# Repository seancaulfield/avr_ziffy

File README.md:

avr_ziffy
=========

Arduino shield with a plethora of ZIF sockets to allow programming of all the
various Atmel AVR chips.

The hardware directory should contain the Eagle CAD project files needed to
build the board. Since they're Not Exactly Code but still open hardware, I'm
licensing them under Creative Commons Attribution Share Alike license.

I've modified the sample code provided with the Arduino distribution for the
firmware files, both because I needed to ensure all the pins would line up and
also do fix a few problems/lack of clarity in the source code Sicne this was
originally under a 2-clause BSD license, I will stick to that for my fork of
the code.

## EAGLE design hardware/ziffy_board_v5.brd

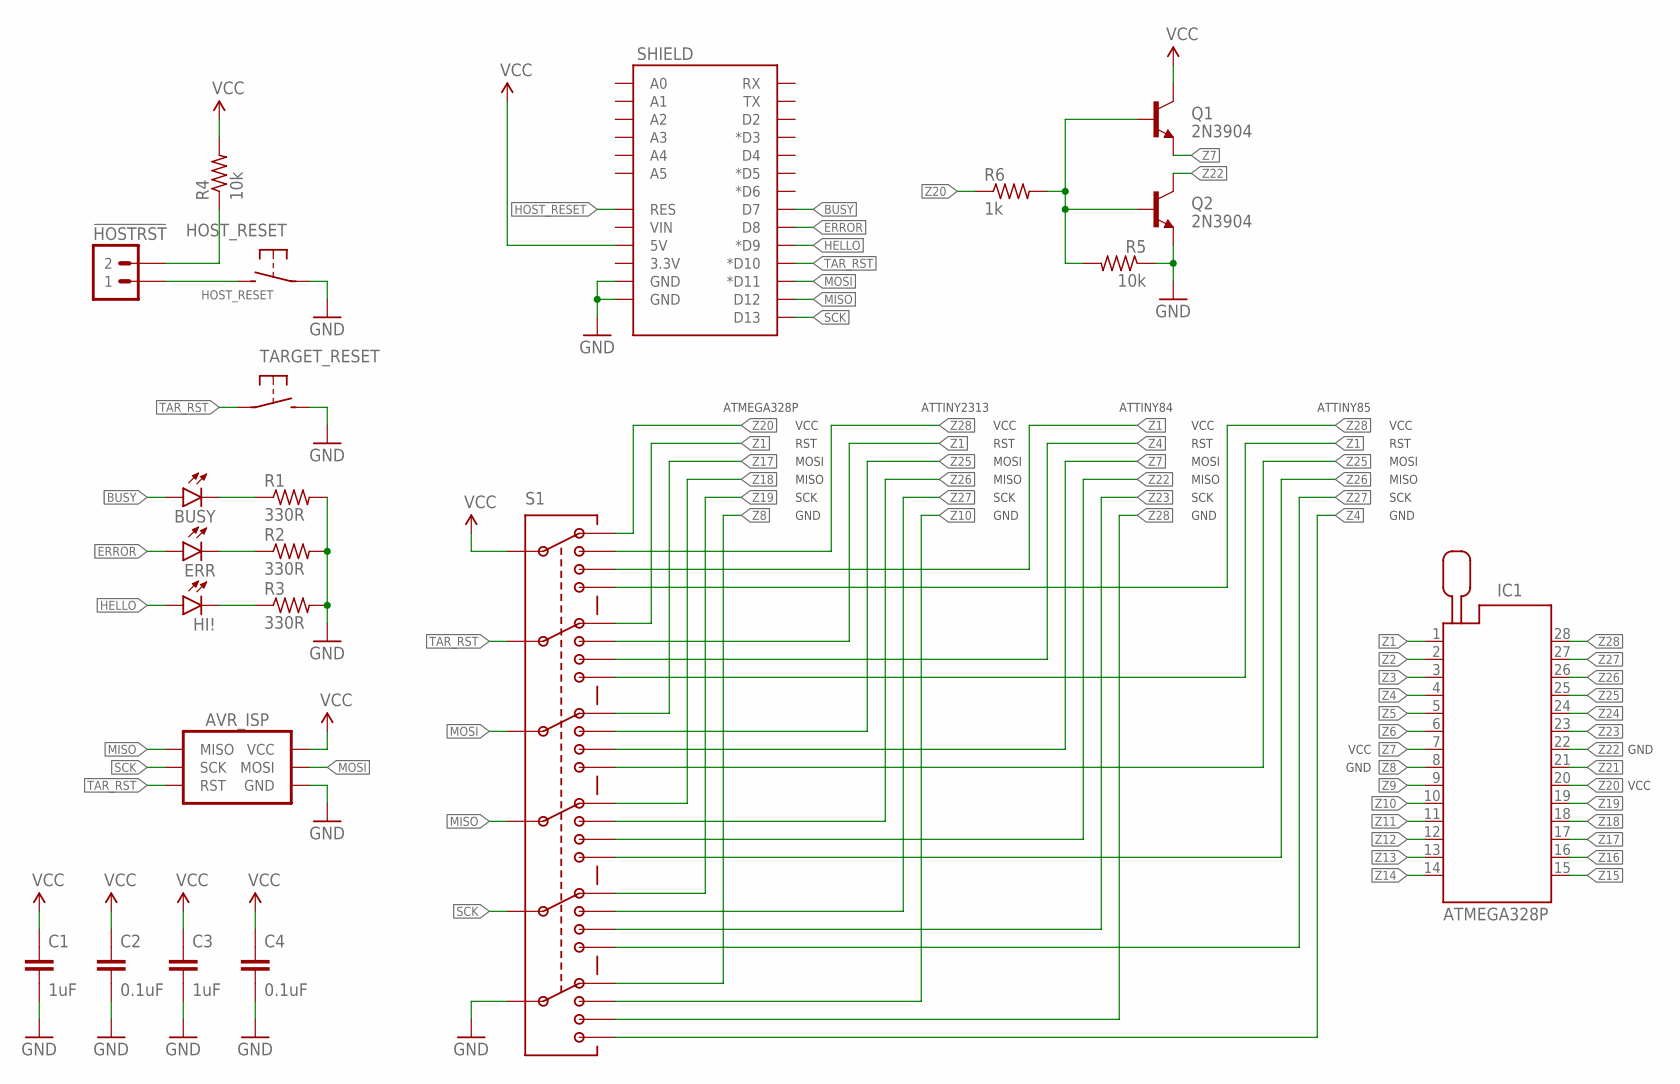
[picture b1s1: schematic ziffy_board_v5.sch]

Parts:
!HOSTRST: M02PTH; 1X02
AVR_ISP: AVR_SPI_PRG_6PTH-SHROUD; 2X3-SHROUDED
BUSY: YELLOW; LED3MM
C1, C3: 1uF; C025-024X044
C2, C4: 0.1uF; C025-024X044
ERR: RED; LED3MM
HI!: GREEN; LED3MM
HOST_RESET: SPST-NO-TACT6MM-PTH-SMALL-PADS; DTS-6-SMALL-PADS
IC1: ATMEGA328P; ZIF28
Q1, Q2: 2N3904; TO-92-AMMO
R1, R2, R3: 330R; RESISTOR-AXIAL-PTH-6.35MM
R4, R5: 10k; RESISTOR-AXIAL-PTH-6.35MM
R6: 1k; RESISTOR-AXIAL-PTH-6.35MM
S1: SWITCH-6P4TASDFADSFSD; SWITCH-6P4T-2MMPTH
SHIELD: ARDUINO_SHIELD_SMALLER; ARDUINO_SHIELD_NOOUTLINE_INSIDE_SMALLER
TARGET_RESET: SPST-NO-TACT6MM-PTH-SMALL-PADS; DTS-6-SMALL-PADS

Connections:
BUSY: BUSY.A, SHIELD.D7
ERROR: ERR.A, SHIELD.D8
GND: AVR_ISP.6 (GND), C1.2, C2.2, C3.2, C4.2, HOST_RESET.1, HOST_RESET.2 (1), Q2.1 (E), R1.P$2 (2), R2.P$2 (2), R3.P$2 (2), R5.P$1 (1), S1.P28 (28), SHIELD.GND@0 (GND), SHIELD.GND@1 (GND), TARGET_RESET.3 (2), TARGET_RESET.4 (2)
HELLO: HI!.A, SHIELD.D9 (*D9)
HOST_RESET: !HOSTRST.1, HOST_RESET.3 (2), HOST_RESET.4 (2), SHIELD.RES
MISO: AVR_ISP.1 (MISO), S1.P18 (18), SHIELD.D12
MOSI: AVR_ISP.4 (MOSI), S1.P13 (13), SHIELD.D11 (*D11)
unnamed: BUSY.K (C), R1.P$1 (1)
unnamed: ERR.K (C), R2.P$1 (1)
unnamed: HI!.K (C), R3.P$1 (1)
unnamed: !HOSTRST.2, R4.P$1 (1)
unnamed: Q1.2 (B), Q2.2 (B), R5.P$2 (2), R6.P$2 (2)
SCK: AVR_ISP.3 (SCK), S1.P23 (23), SHIELD.D13
TAR_RST: AVR_ISP.5 (RST), S1.P8 (8), SHIELD.D10 (*D10), TARGET_RESET.1, TARGET_RESET.2 (1)
VCC: AVR_ISP.2 (VCC), C1.1, C2.1, C3.1, C4.1, Q1.3 (C), R4.P$2 (2), S1.P3 (3), SHIELD.5V
Z1: IC1.1, S1.P4 (4), S1.P6 (6), S1.P7 (7), S1.P10 (10)
Z2: IC1.2
Z3: IC1.3
Z4: IC1.4, S1.P9 (9), S1.P30 (30)
Z5: IC1.5
Z6: IC1.6
Z7: IC1.7, Q1.1 (E), S1.P14 (14)
Z8: IC1.8, S1.P26 (26)
Z9: IC1.9
Z10: IC1.10, S1.P27 (27)
Z11: IC1.11
Z12: IC1.12
Z13: IC1.13
Z14: IC1.14
Z15: IC1.15
Z16: IC1.16
Z17: IC1.17, S1.P11 (11)
Z18: IC1.18, S1.P16 (16)
Z19: IC1.19, S1.P21 (21)
Z20: IC1.20, R6.P$1 (1), S1.P1 (1)
Z21: IC1.21
Z22: IC1.22, Q2.3 (C), S1.P19 (19)
Z23: IC1.23, S1.P24 (24)
Z24: IC1.24
Z25: IC1.25, S1.P12 (12), S1.P15 (15)
Z26: IC1.26, S1.P17 (17), S1.P20 (20)
Z27: IC1.27, S1.P22 (22), S1.P25 (25)
Z28: IC1.28, S1.P2 (2), S1.P5 (5), S1.P29 (29)

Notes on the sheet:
ATMEGA328P
ATTINY2313
ATTINY84
ATTINY85
VCC
RST
MOSI
MISO
SCK
GND

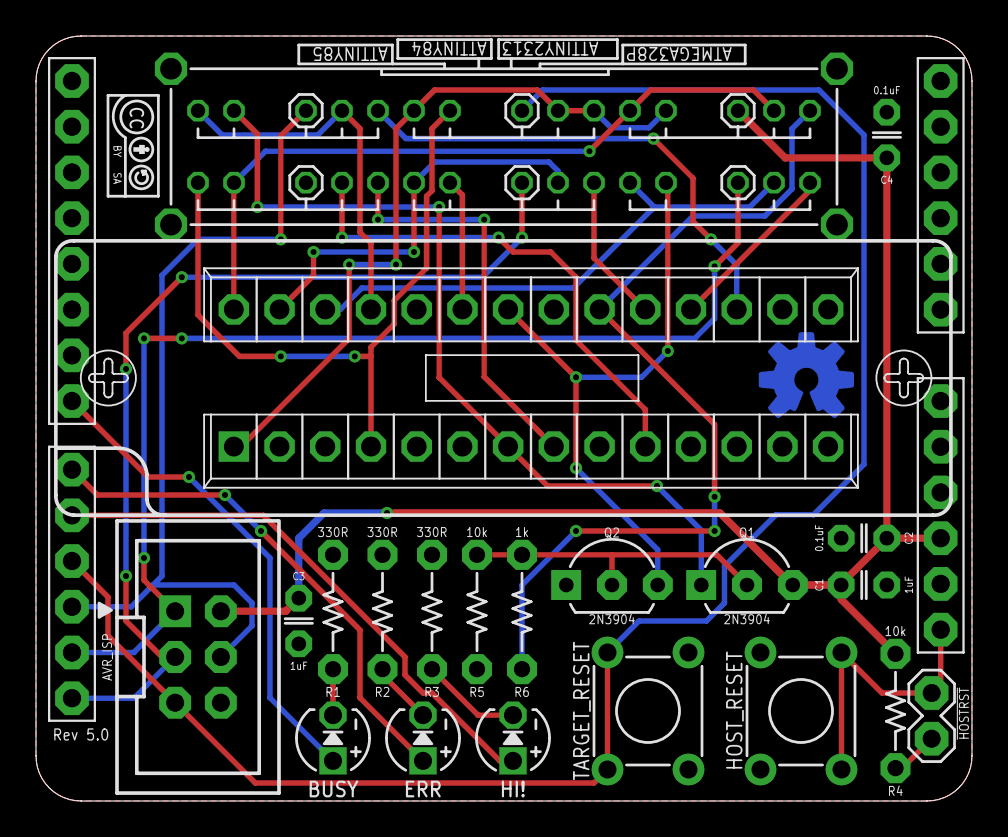
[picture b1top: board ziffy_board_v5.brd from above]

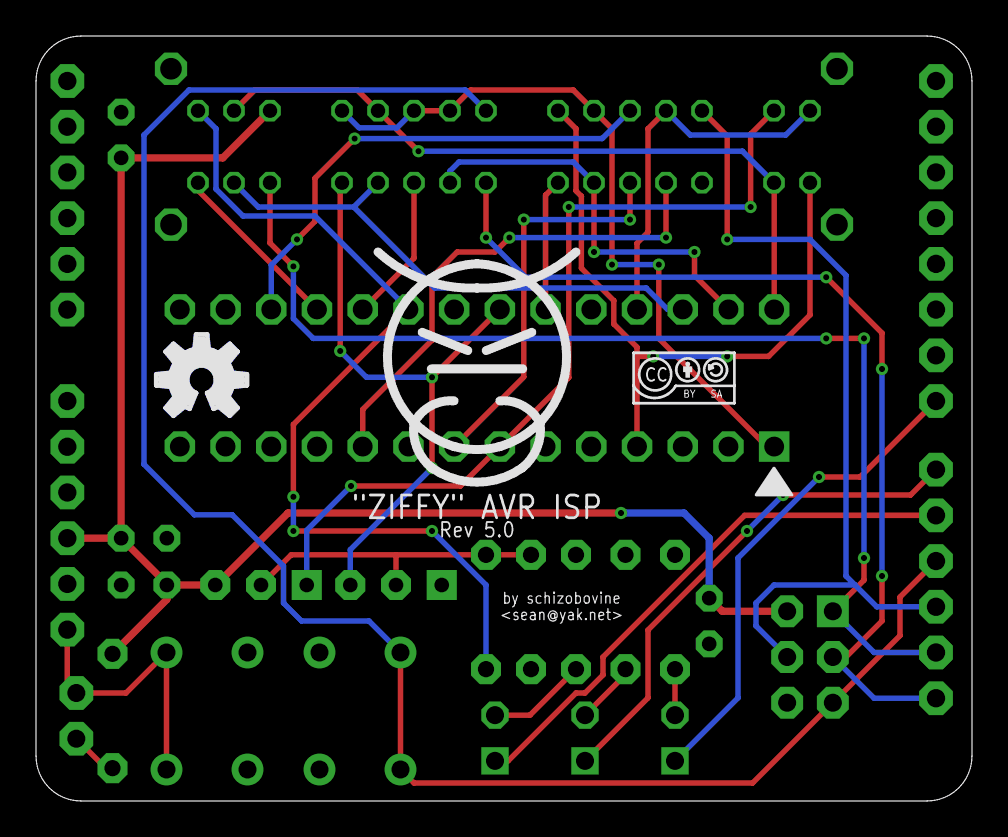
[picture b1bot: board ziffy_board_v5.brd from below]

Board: 2 copper layers, 52.0 x 42.5 mm, 26 parts (2 on the bottom side), 30 nets.

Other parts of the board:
U$1, U$5: CC-BY-SA-4.0-NO-URL
U$2: COW
U$3: OSHWLOGO_BOT_0.2

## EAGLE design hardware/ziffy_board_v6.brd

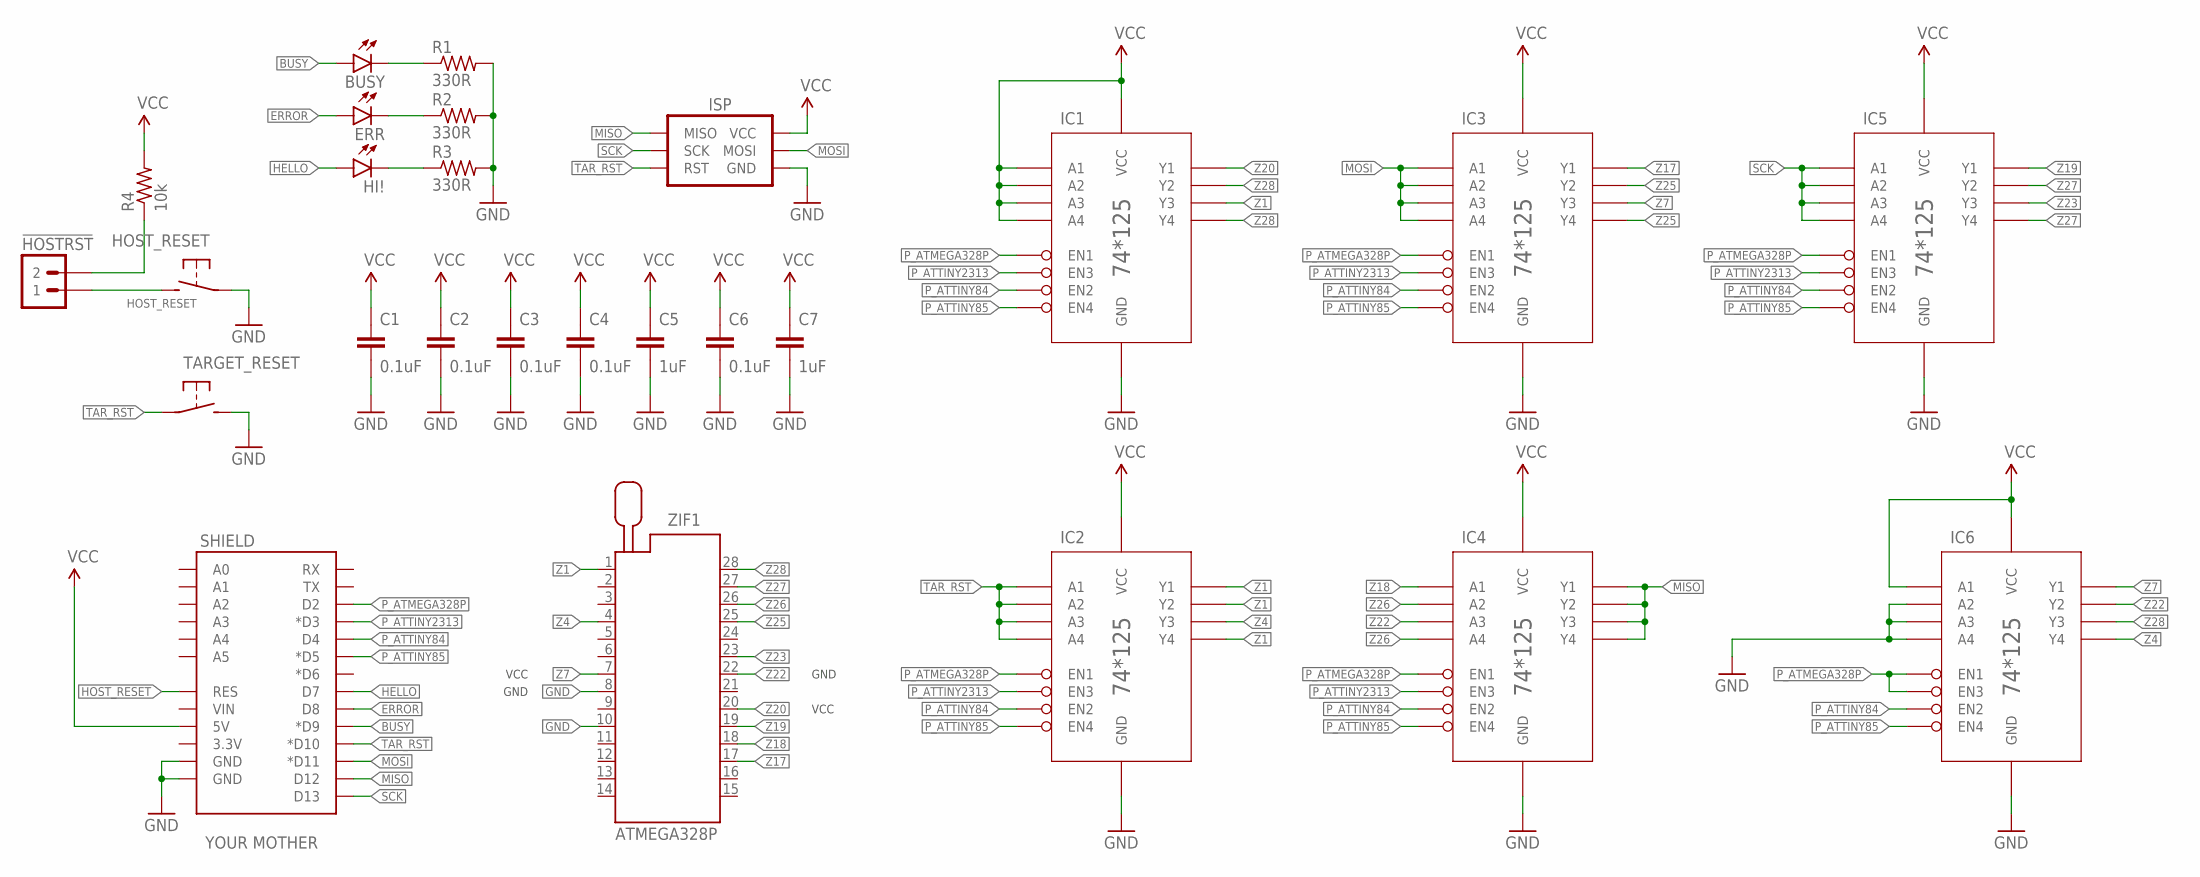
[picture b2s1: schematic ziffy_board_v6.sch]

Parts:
!HOSTRST: M02PTH; 1X02
BUSY: YELLOW; LED3MM
C1, C2, C3, C4, C6: 0.1uF; C025-024X044
C5, C7: 1uF; C025-024X044
ERR: RED; LED3MM
HI!: GREEN; LED3MM
HOST_RESET: SPST-NO-TACT6MM-PTH-SMALL-PADS; DTS-6-SMALL-PADS
IC1, IC2, IC3, IC4, IC5, IC6: 74HC125; SO14
ISP: AVR_SPI_PRG_6PTH-SHROUD; 2X3-SHROUDED
R1, R2, R3: 330R; RESISTOR-AXIAL-PTH-5.08MM
R4: 10k; RESISTOR-AXIAL-PTH-5.08MM
SHIELD: YOUR MOTHER; ARDUINO_SHIELD_NOOUTLINE_INSIDE_SMALLER
TARGET_RESET: SPST-NO-TACT6MM-PTH-SMALL-PADS; DTS-6-SMALL-PADS
ZIF1: ATMEGA328P; ZIF28

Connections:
BUSY: BUSY.A, SHIELD.D9 (*D9)
ERROR: ERR.A, SHIELD.D8
GND: C1.2, C2.2, C3.2, C4.2, C5.2, C6.2, C7.2, HOST_RESET.1, HOST_RESET.2 (1), IC1.7 (GND), IC2.7 (GND), IC3.7 (GND), IC4.7 (GND), IC5.7 (GND), IC6.5 (A2), IC6.7 (GND), IC6.9 (A3), IC6.12 (A4), ISP.6 (GND), R1.P$2 (2), R2.P$2 (2), R3.P$2 (2), SHIELD.GND@0 (GND), SHIELD.GND@1 (GND), TARGET_RESET.3 (2), TARGET_RESET.4 (2), ZIF1.8, ZIF1.10
HELLO: HI!.A, SHIELD.D7
HOST_RESET: !HOSTRST.1, HOST_RESET.3 (2), HOST_RESET.4 (2), SHIELD.RES
MISO: IC4.3 (Y1), IC4.6 (Y2), IC4.8 (Y3), IC4.11 (Y4), ISP.1 (MISO), SHIELD.D12
MOSI: IC3.2 (A1), IC3.5 (A2), IC3.9 (A3), IC3.12 (A4), ISP.4 (MOSI), SHIELD.D11 (*D11)
unnamed: BUSY.K (C), R1.P$1 (1)
unnamed: ERR.K (C), R2.P$1 (1)
unnamed: HI!.K (C), R3.P$1 (1)
unnamed: !HOSTRST.2, R4.P$1 (1)
P_ATMEGA328P: IC1.1 (EN1), IC2.1 (EN1), IC3.1 (EN1), IC4.1 (EN1), IC5.1 (EN1), IC6.1 (EN1), IC6.10 (EN3), SHIELD.D2
P_ATTINY84: IC1.4 (EN2), IC2.4 (EN2), IC3.4 (EN2), IC4.4 (EN2), IC5.4 (EN2), IC6.4 (EN2), SHIELD.D4
P_ATTINY85: IC1.13 (EN4), IC2.13 (EN4), IC3.13 (EN4), IC4.13 (EN4), IC5.13 (EN4), IC6.13 (EN4), SHIELD.D5 (*D5)
P_ATTINY2313: IC1.10 (EN3), IC2.10 (EN3), IC3.10 (EN3), IC4.10 (EN3), IC5.10 (EN3), SHIELD.D3 (*D3)
SCK: IC5.2 (A1), IC5.5 (A2), IC5.9 (A3), IC5.12 (A4), ISP.3 (SCK), SHIELD.D13
TAR_RST: IC2.2 (A1), IC2.5 (A2), IC2.9 (A3), IC2.12 (A4), ISP.5 (RST), SHIELD.D10 (*D10), TARGET_RESET.1, TARGET_RESET.2 (1)
VCC: C1.1, C2.1, C3.1, C4.1, C5.1, C6.1, C7.1, IC1.2 (A1), IC1.5 (A2), IC1.9 (A3), IC1.12 (A4), IC1.14 (VCC), IC2.14 (VCC), IC3.14 (VCC), IC4.14 (VCC), IC5.14 (VCC), IC6.2 (A1), IC6.14 (VCC), ISP.2 (VCC), R4.P$2 (2), SHIELD.5V
Z1: IC1.8 (Y3), IC2.3 (Y1), IC2.6 (Y2), IC2.11 (Y4), ZIF1.1
Z4: IC2.8 (Y3), IC6.11 (Y4), ZIF1.4
Z7: IC3.8 (Y3), IC6.3 (Y1), ZIF1.7
Z17: IC3.3 (Y1), ZIF1.17
Z18: IC4.2 (A1), ZIF1.18
Z19: IC5.3 (Y1), ZIF1.19
Z20: IC1.3 (Y1), ZIF1.20
Z22: IC4.9 (A3), IC6.6 (Y2), ZIF1.22
Z23: IC5.8 (Y3), ZIF1.23
Z25: IC3.6 (Y2), IC3.11 (Y4), ZIF1.25
Z26: IC4.5 (A2), IC4.12 (A4), ZIF1.26
Z27: IC5.6 (Y2), IC5.11 (Y4), ZIF1.27
Z28: IC1.6 (Y2), IC1.11 (Y4), IC6.8 (Y3), ZIF1.28

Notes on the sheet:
VCC
GND

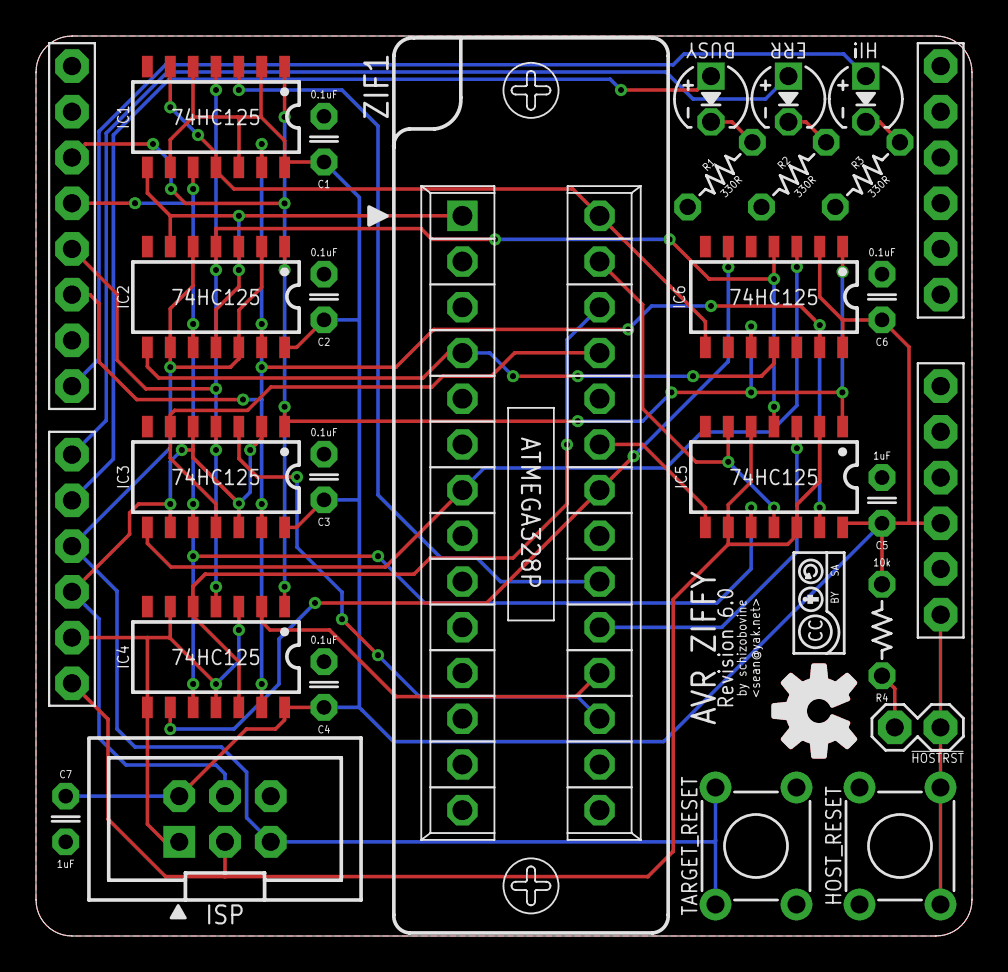
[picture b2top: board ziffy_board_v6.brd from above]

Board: 2 copper layers, 52.0 x 50.0 mm, 28 parts (0 on the bottom side), 31 nets.

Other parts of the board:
U$1: CC-BY-SA-4.0-NO-URL
U$2: OSHWLOGO_TOP_0.2_A

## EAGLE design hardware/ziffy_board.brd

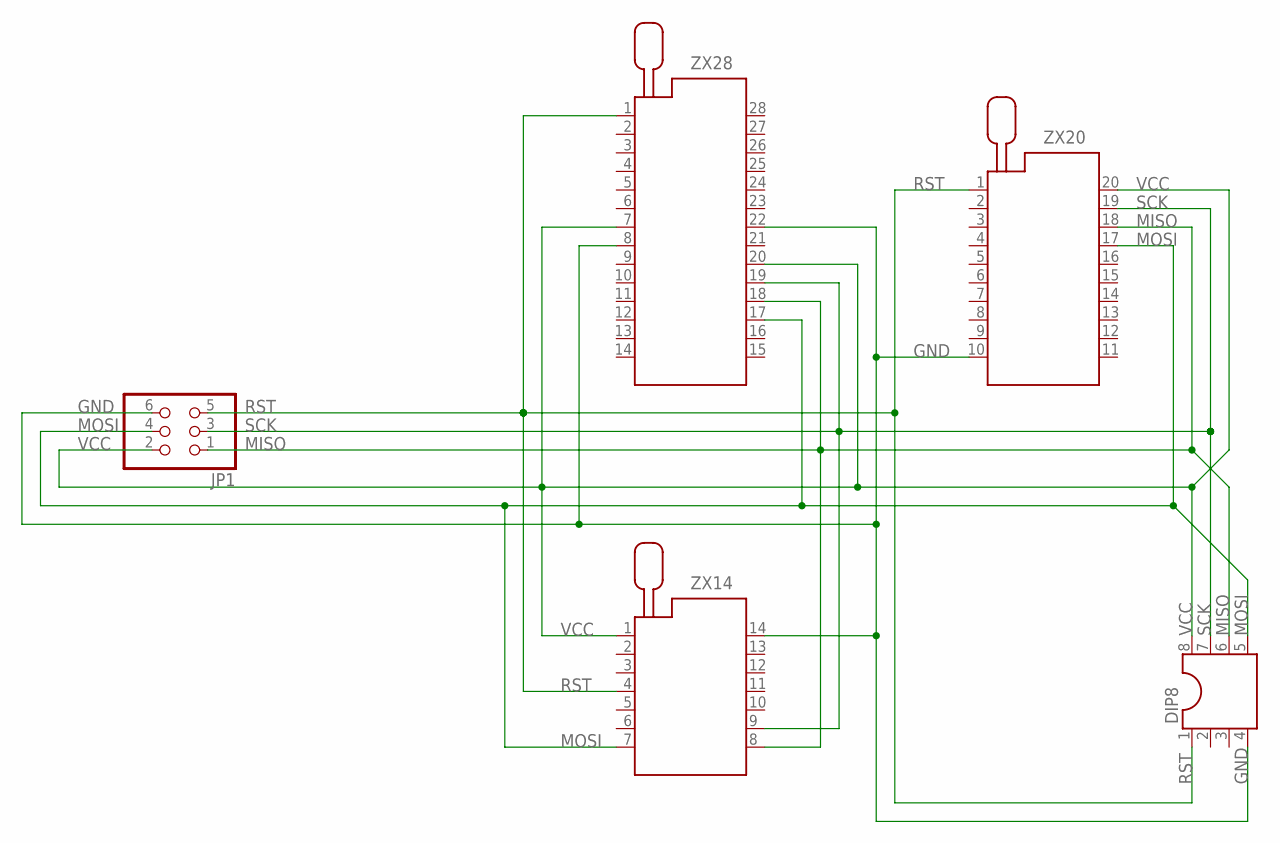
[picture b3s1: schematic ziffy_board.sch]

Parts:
DIP8: DIL8S; SOCKET-08
JP1: PINHD-2X3; 2X03
ZX14: 214-3339-00-0602J
ZX20: 220-3342-00-0602J
ZX28: 228-4817-00-0602J

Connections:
GND: DIP8.4, JP1.6, ZX14.14, ZX20.10, ZX28.8, ZX28.22
MISO: DIP8.6, JP1.1, ZX14.8, ZX20.18, ZX28.18
MOSI: DIP8.5, JP1.4, ZX14.7, ZX20.17, ZX28.17
RST: DIP8.1, JP1.5, ZX14.4, ZX20.1, ZX28.1
SCK: DIP8.7, JP1.3, ZX14.9, ZX20.19, ZX28.19
VCC: DIP8.8, JP1.2, ZX14.1, ZX20.20, ZX28.7, ZX28.20

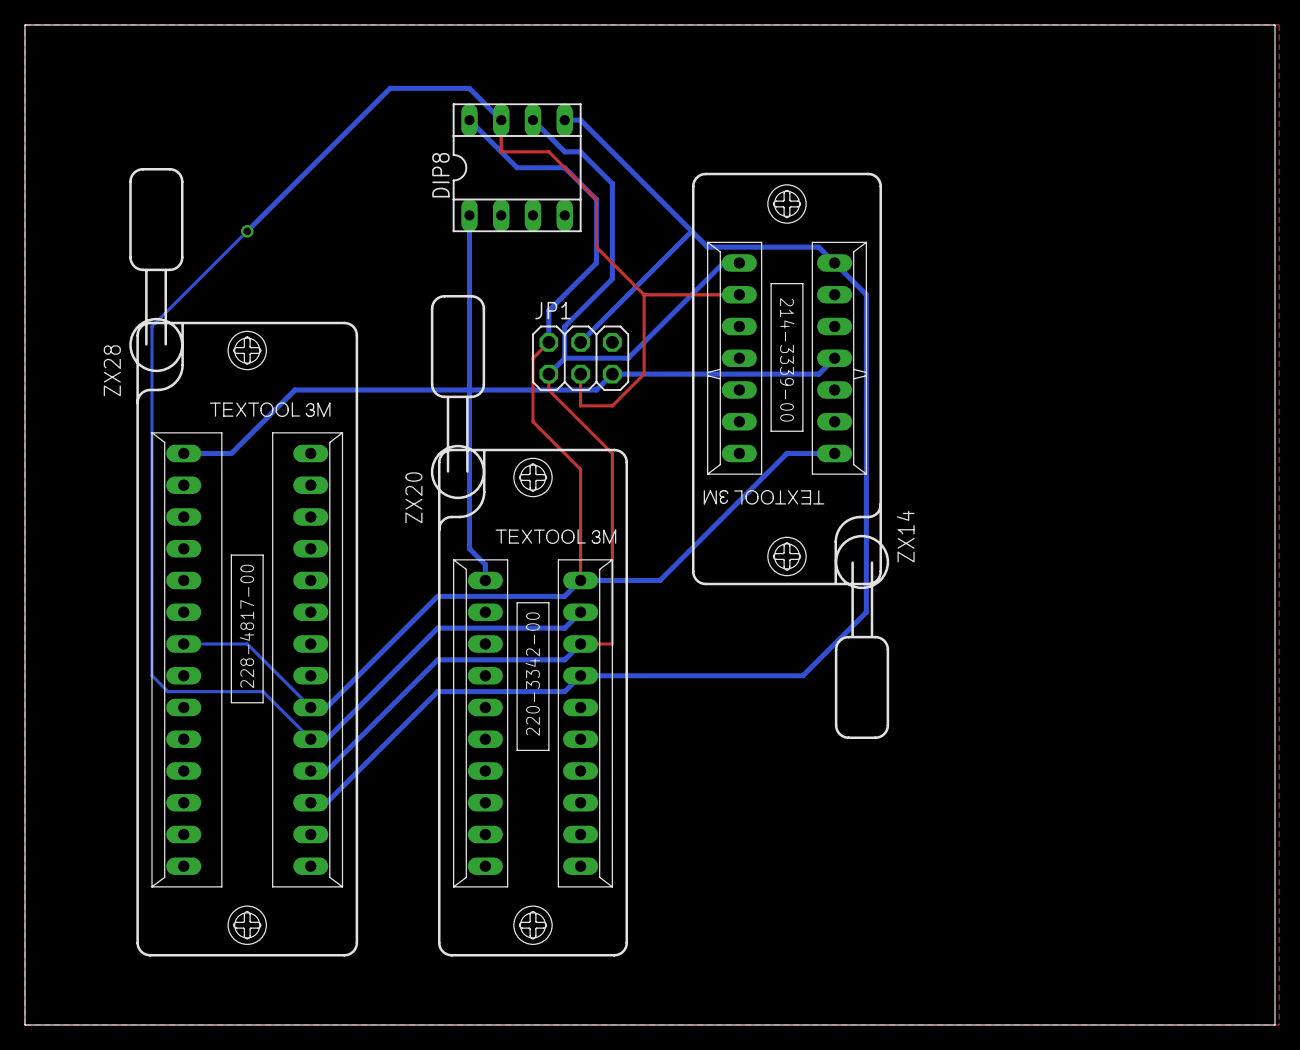
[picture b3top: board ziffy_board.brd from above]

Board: 2 copper layers, 100.0 x 80.0 mm, 5 parts (0 on the bottom side), 6 nets.

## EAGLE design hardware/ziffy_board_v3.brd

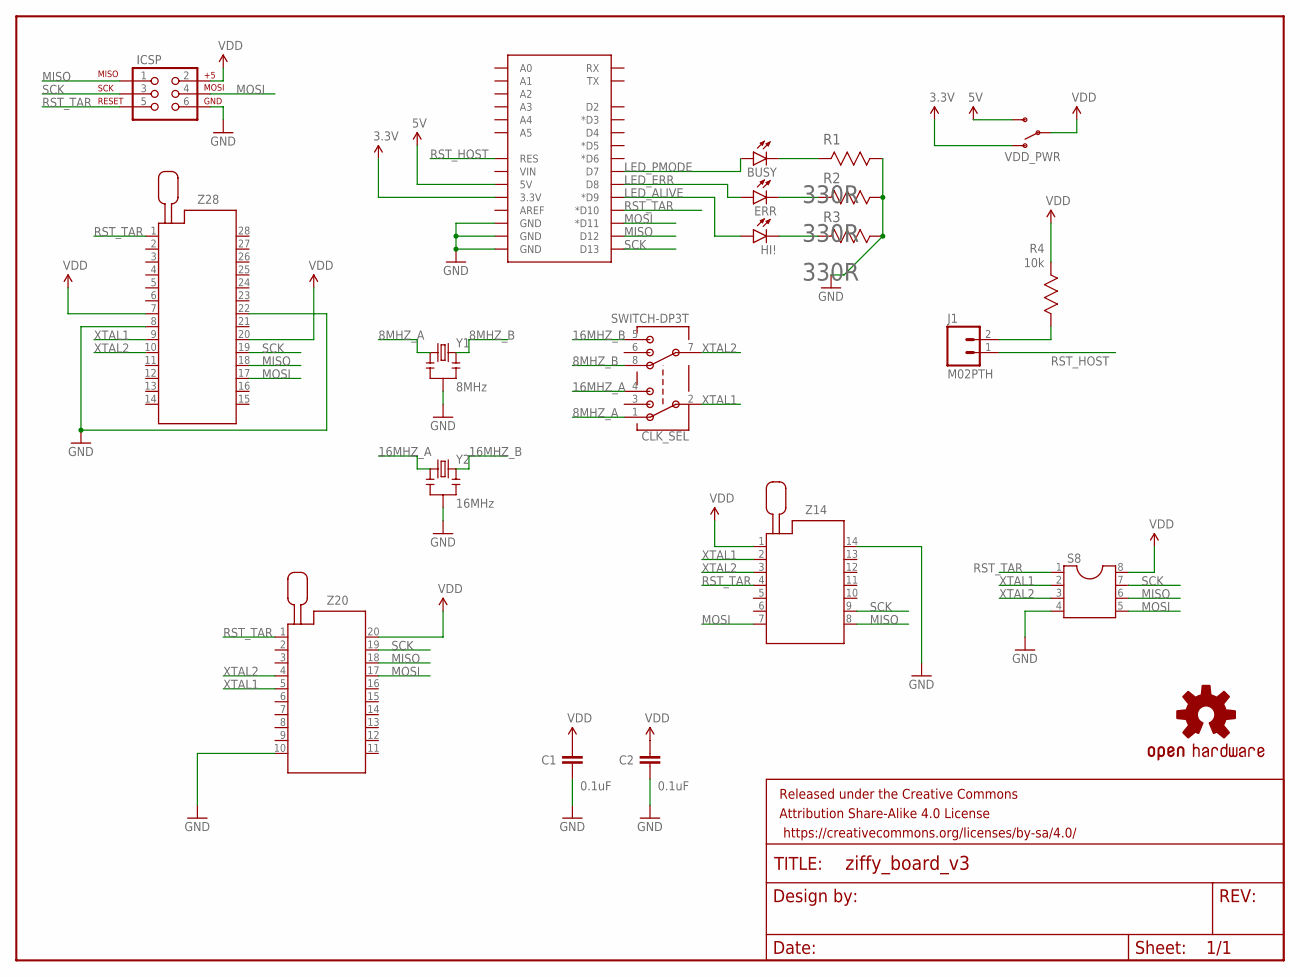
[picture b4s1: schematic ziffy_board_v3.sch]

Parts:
BUSY: YELLOW; LED3MM
C1, C2: 0.1uF; CAP-PTH-SMALL2
CLK_SEL: SWITCH-DP3T
ERR: RED; LED3MM
FRAME1: FRAME-LETTER; CREATIVE_COMMONS
HI!: GREEN; LED3MM
ICSP: AVR_SPI_PRG_6PTH; 2X3
J1: M02PTH; 1X02
LOGO2: OSHW-LOGOS; OSHW-LOGO-S
R1, R2, R3: 330R; AXIAL-0.2
R4: 10k; AXIAL-0.2
S8: DIPSHIT; DIL08
U$1: ARDUINO_SHIELDOUTLINE_NOHOLES; ARDUINO_SHIELD_OUTLINE_NOHOLES
VDD_PWR: SPDT; SWITCH-SPDT
Y1: 8MHz; RESONATOR-PTH
Y2: 16MHz; RESONATOR-PTH
Z14: ZIF14
Z20: ZIF20
Z28: ZIF28

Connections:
3.3V: U$1.3.3V, VDD_PWR.1 (O)
5V: U$1.5V, VDD_PWR.3 (S)
8MHZ_A: CLK_SEL.1, Y1.1
8MHZ_B: CLK_SEL.8, Y1.3
16MHZ_A: CLK_SEL.4, Y2.1
16MHZ_B: CLK_SEL.5, Y2.3
GND: C1.2, C2.2, ICSP.6, R1.P$1 (2), R2.P$1 (2), R3.P$1 (2), S8.4, U$1.GND@0 (GND), U$1.GND@1 (GND), U$1.GND@2 (GND), Y1.2, Y2.2, Z14.14, Z20.10, Z28.8, Z28.22
LED_ALIVE: HI!.A, U$1.D9 (*D9)
LED_ERR: ERR.A, U$1.D8
LED_PMODE: BUSY.A, U$1.D7
MISO: ICSP.1, S8.6, U$1.D12, Z14.8, Z20.18, Z28.18
MOSI: ICSP.4, S8.5, U$1.D11 (*D11), Z14.7, Z20.17, Z28.17
unnamed: BUSY.K (C), R1.P$2 (1)
unnamed: ERR.K (C), R2.P$2 (1)
unnamed: HI!.K (C), R3.P$2 (1)
unnamed: J1.2, R4.P$1 (2)
RST_HOST: J1.1, U$1.RES
RST_TAR: ICSP.5, S8.1, U$1.D10 (*D10), Z14.4, Z20.1, Z28.1
SCK: ICSP.3, S8.7, U$1.D13, Z14.9, Z20.19, Z28.19
VDD: C1.1, C2.1, ICSP.2, R4.P$2 (1), S8.8, VDD_PWR.2, Z14.1, Z20.20, Z28.7, Z28.20
XTAL1: CLK_SEL.2, S8.2, Z14.2, Z20.5, Z28.9
XTAL2: CLK_SEL.7, S8.3, Z14.3, Z20.4, Z28.10

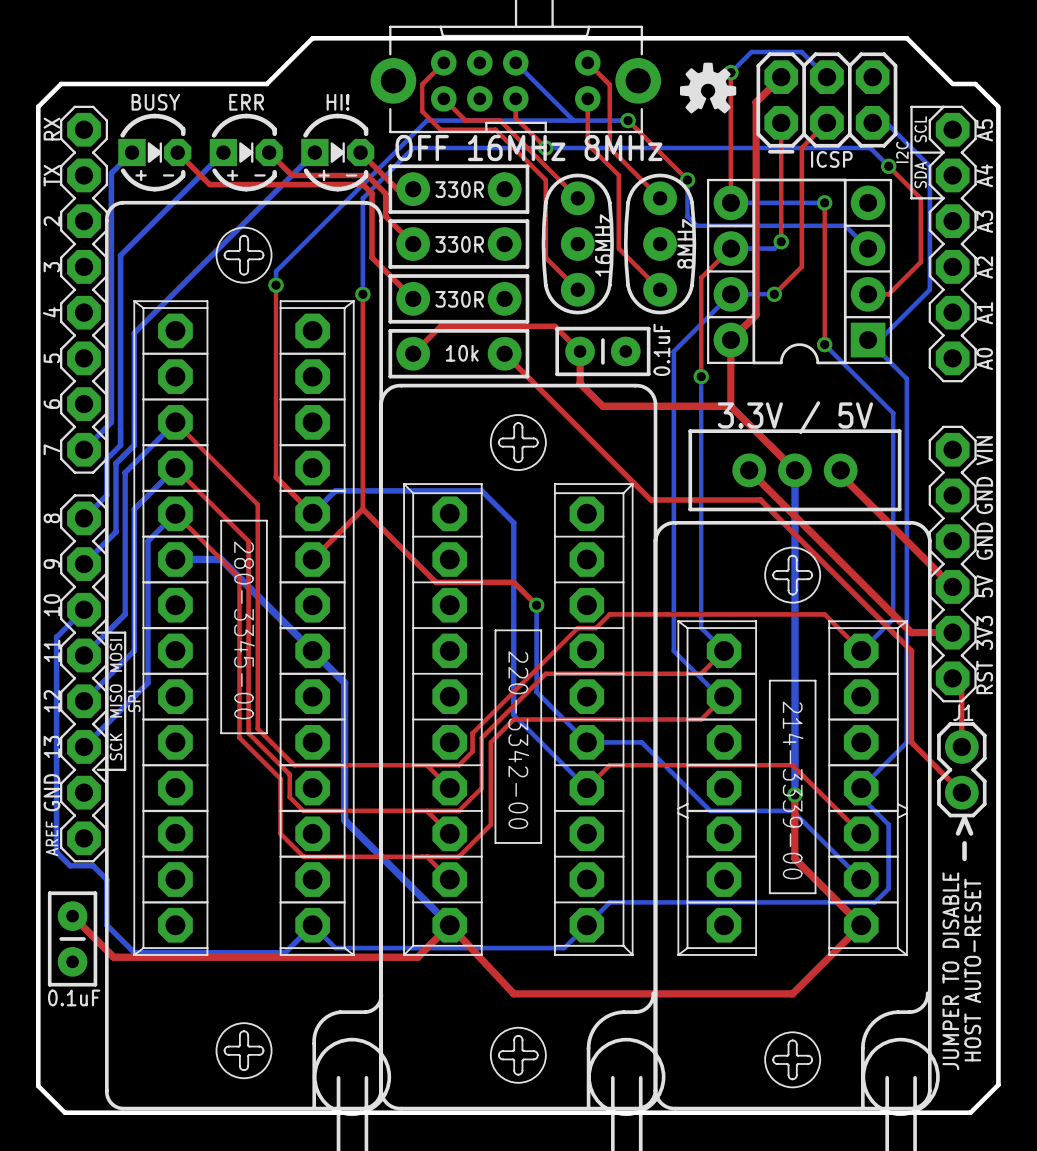
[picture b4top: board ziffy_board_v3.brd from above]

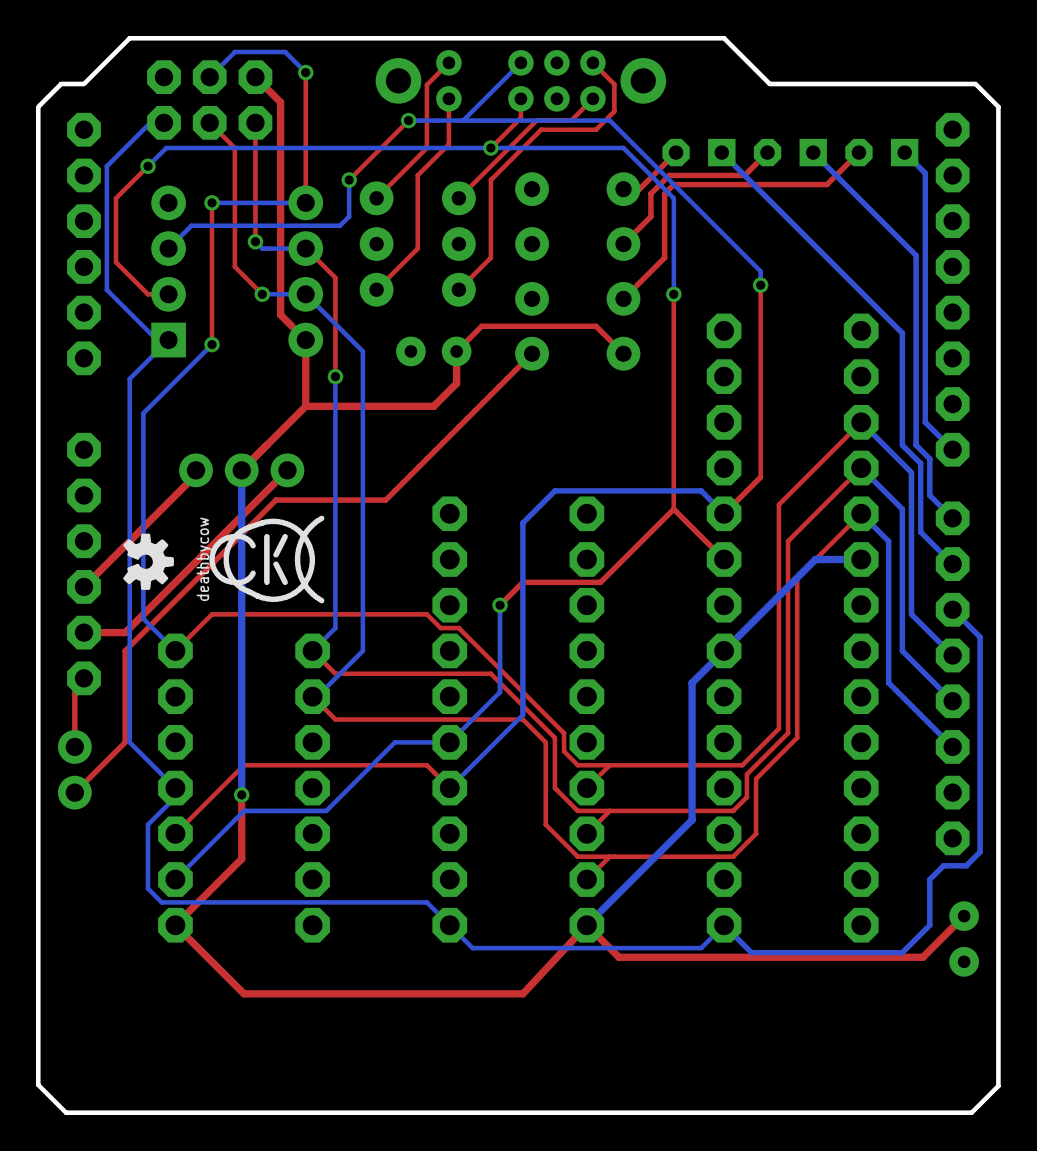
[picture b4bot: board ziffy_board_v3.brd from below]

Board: 2 copper layers, 53.3 x 59.7 mm, 24 parts (2 on the bottom side), 22 nets.

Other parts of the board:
LOGO1: OSHW-LOGOS; OSHW-LOGO-S
U$3: COW_SMALL

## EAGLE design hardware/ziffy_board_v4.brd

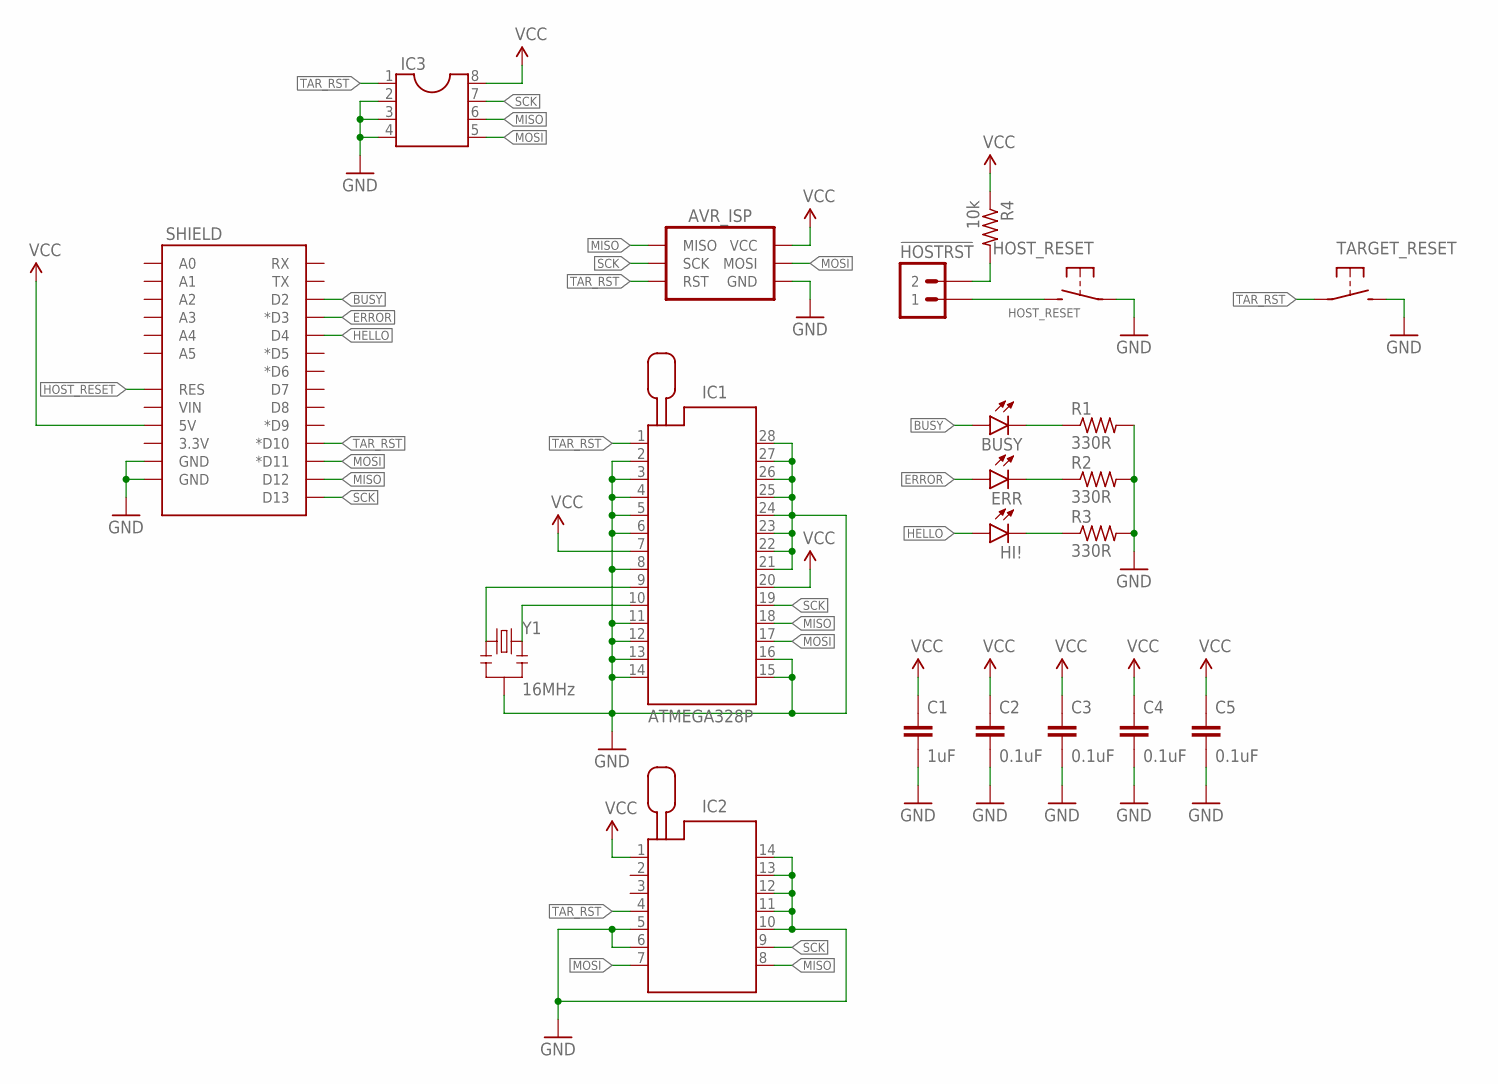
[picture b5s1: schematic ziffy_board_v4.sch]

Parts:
!HOSTRST: M02PTH; 1X02
AVR_ISP: AVR_SPI_PRG_6PTH-SHROUD; 2X3-SHROUDED
BUSY: YELLOW; LED3MM
C1: 1uF; C025-024X044
C2, C3, C4, C5: 0.1uF; C025-024X044
ERR: RED; LED3MM
HI!: GREEN; LED3MM
HOST_RESET: SPST-NO-TACT3MM-PTH-SMALL-PADS; DTS-3-SMALL-PADS
IC1: ATMEGA328P; ZIF28
IC2: ATTINY84; ZIF14
IC3: DIL8; DIL08
R1, R2, R3: 330R; RESISTOR-AXIAL-PTH-6.35MM
R4: 10k; RESISTOR-AXIAL-PTH-5.08MM
SHIELD: ARDUINO_SHIELD_SMALLER; ARDUINO_SHIELD_NOOUTLINE_INSIDE_SMALLER
TARGET_RESET: SPST-NO-TACT3MM-PTH-SMALL-PADS; DTS-3-SMALL-PADS
Y1: 16MHz; RESONATOR-PTH

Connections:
BUSY: BUSY.A, SHIELD.D2
ERROR: ERR.A, SHIELD.D3 (*D3)
GND: AVR_ISP.6 (GND), C1.2, C2.2, C3.2, C4.2, C5.2, HOST_RESET.1, IC1.2, IC1.3, IC1.4, IC1.5, IC1.6, IC1.8, IC1.11, IC1.12, IC1.13, IC1.14, IC1.15, IC1.16, IC1.21, IC1.22, IC1.23, IC1.24, IC1.25, IC1.26, IC1.27, IC1.28, IC2.5, IC2.6, IC2.10, IC2.11, IC2.12, IC2.13, IC2.14, IC3.2, IC3.3, IC3.4, R1.P$2 (2), R2.P$2 (2), R3.P$2 (2), SHIELD.GND@0 (GND), SHIELD.GND@1 (GND), TARGET_RESET.2, Y1.2
HELLO: HI!.A, SHIELD.D4
HOST_RESET: !HOSTRST.1, HOST_RESET.2, SHIELD.RES
MISO: AVR_ISP.1 (MISO), IC1.18, IC2.8, IC3.6, SHIELD.D12
MOSI: AVR_ISP.4 (MOSI), IC1.17, IC2.7, IC3.5, SHIELD.D11 (*D11)
unnamed: BUSY.K (C), R1.P$1 (1)
unnamed: ERR.K (C), R2.P$1 (1)
unnamed: HI!.K (C), R3.P$1 (1)
unnamed: !HOSTRST.2, R4.P$2 (2)
unnamed: IC1.9, Y1.1
unnamed: IC1.10, Y1.3
SCK: AVR_ISP.3 (SCK), IC1.19, IC2.9, IC3.7, SHIELD.D13
TAR_RST: AVR_ISP.5 (RST), IC1.1, IC2.4, IC3.1, SHIELD.D10 (*D10), TARGET_RESET.1
VCC: AVR_ISP.2 (VCC), C1.1, C2.1, C3.1, C4.1, C5.1, IC1.7, IC1.20, IC2.1, IC3.8, R4.P$1 (1), SHIELD.5V

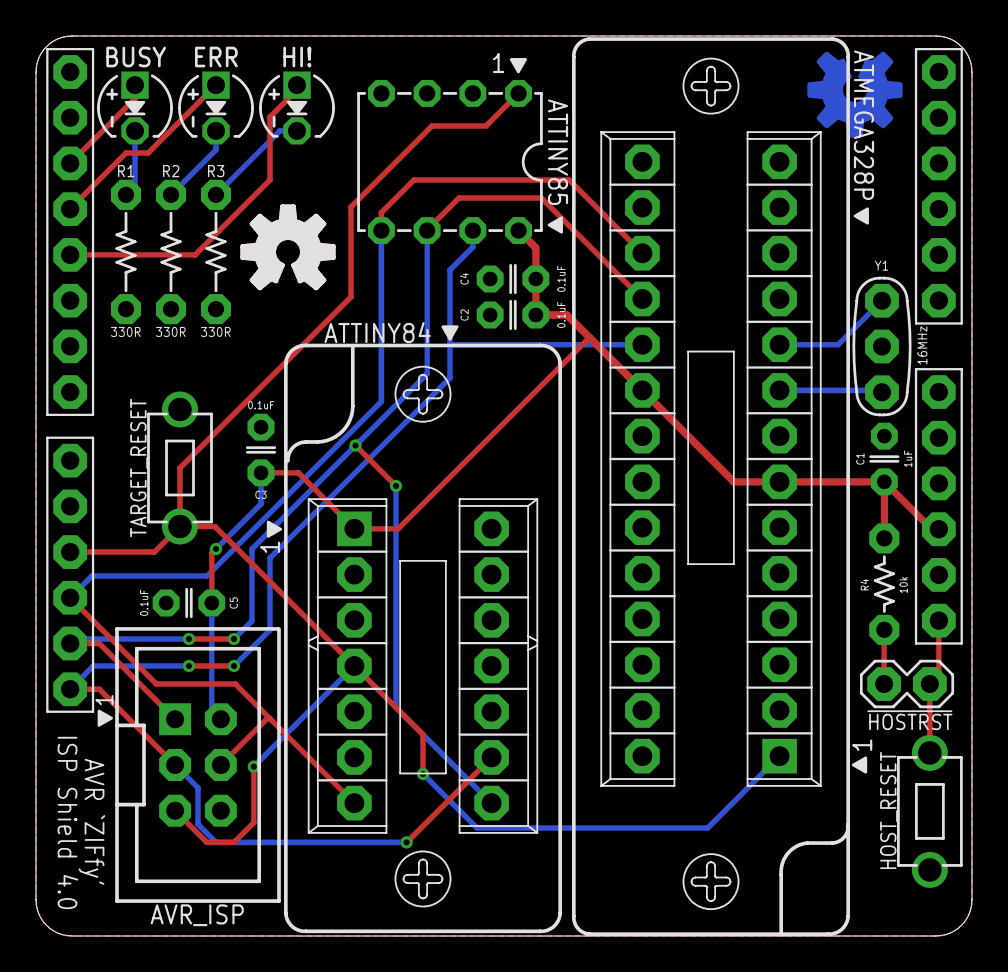
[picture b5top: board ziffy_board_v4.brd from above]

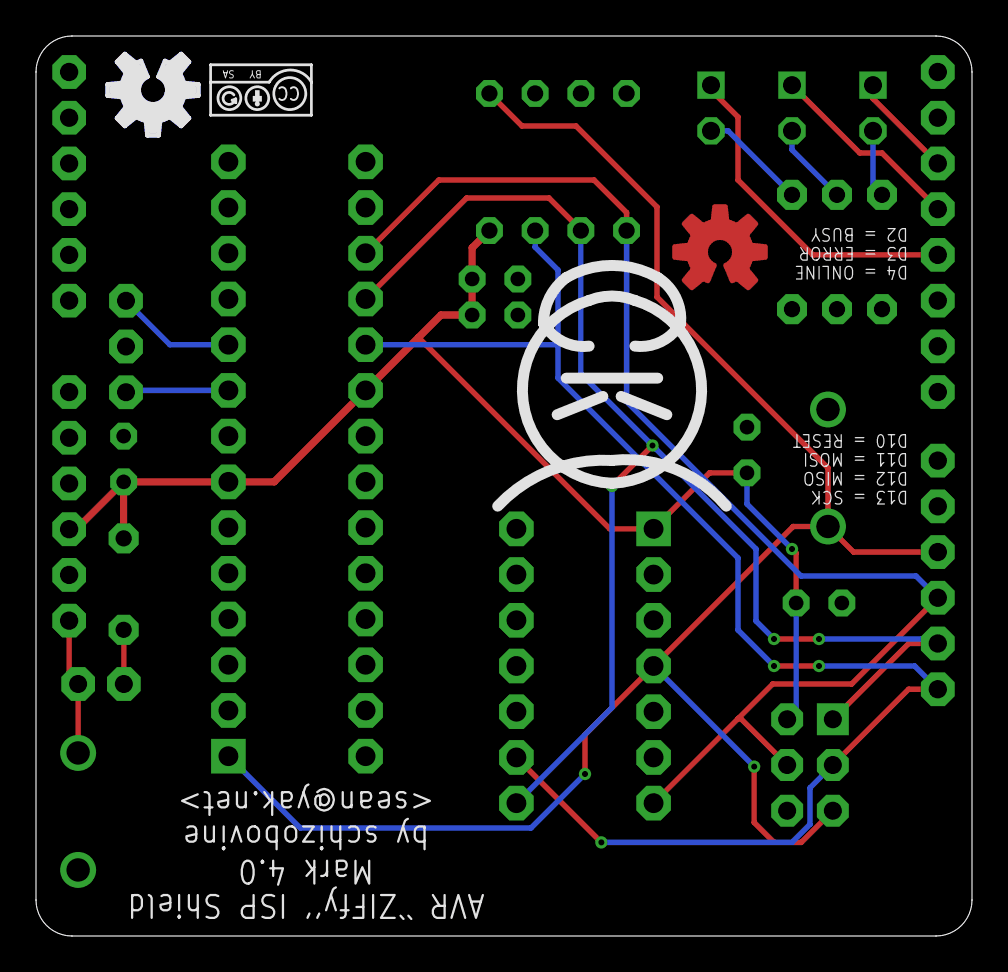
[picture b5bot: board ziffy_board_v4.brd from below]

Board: 2 copper layers, 52.0 x 50.0 mm, 25 parts (3 on the bottom side), 16 nets.

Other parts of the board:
U$2: CC-BY-SA-4.0-NO-URL
U$3: COW
U$5, U$6: OSHWLOGO_TOP_0.2

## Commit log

2014-09-23 initial import of firmware code (i've been bad so you don't get the fork/modifications diff from the mainline until I can find it)
2014-12-23 Initial commit of first four (!) PCB revs.
    1.0) Never saw production, unfinished.
    2.0) Fabbed, but holes for ZIF sockets & many other components far too
    small. What I get for not measuring. :P
    3.0) Holes enlarged, relayout, etc. Works kinda, but clock stuff is
    completely bogus since I added a motherfuckton of parasitic
    capacitance/inductance with all those traces. If your chip expects a
2014-12-23 initial firmware checkin with minor tweaks from the arduino dist to get it to compile and eliminate some errors
2014-12-23 changing pin defs for rev4 board
2014-12-23 adding eagle description file
2014-12-26 mark 5 now with physical big-ass switch. vcc routing done only
2014-12-26 most routing complete, just the ratsnest near the switch left (ugh)
2014-12-27 new version using bus drivers
2014-12-27 layout complete for mark 5
2015-01-09 tweaked
2015-01-11 more twaddling
2015-01-11 routing done! mostly. now trying to return to pin-compat with original code base
2015-01-11 more trying to return to pin-compat with original code base
2015-01-11 layout complete. replaced most of the surface mount caps w/PTH ones. still debating resistors for LEDs.
2015-01-11 trying all the angles (ba-dum-tish)
2015-01-11 re-layered values so they actually make it to the silkscreen layer
2015-01-11 update the damn library b/c apparently i hadn't merged all teh changes from there either.
2015-01-12 touch ups, edge routering, etc.
2015-01-12 silk screen, ready for fab i think
2015-01-12 oshpark: wat
2015-01-12 updating description for various revisions. .md file is markdown for oshpark.

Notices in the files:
parts and their libraries:
SparkFun-Connectors: Licensing: Creative Commons ShareAlike 4.0 International - https://creativecommons.org/licenses/by-sa/4.0
SparkFun-Aesthetics: Released under the Creative Commons Attribution Share-Alike 4.0 License
SparkFun-Aesthetics: https://creativecommons.org/licenses/by-sa/4.0
